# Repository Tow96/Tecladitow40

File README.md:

# Tecladitow-40

The Tecladitow40 is a simple 40% handwired ortholinear keyboard which utilizes 
[QMK](https://github.com/qmk/qmk_firmware) to communicate with any USB capable 
device. The Tecladitow40 is based on a Teensy2.0 microcontroller.

## Repository structure
The repository is divided in two subfolders, each containing a different part of 
the project. Further documentation can be found inside these folders.

1. [**Assembly**](/Assembly) - This folder contains the files that make up the 
physical keyboard. They are available in .SLDPRT and .STL formats.

2. [**Firmware**](/Firmware) - This folder contains the Hex file used to flash the
keyboard as well as a simple Test program to check the functionality of the keys.

## Future improvements
The specific improvements are separated by category inside the documentation for each folder.

- [ ] **Make rev1:** This revision will change the microcontroller to a pure 
ATmega32u4 and have a pcb.

## Credits
- Jose Tow [[@Tow96](https://github.com/Tow96)]

## License
This project is licensed under [GNU GPL-3.0](/LICENSE) as I believe in open source 
projects.

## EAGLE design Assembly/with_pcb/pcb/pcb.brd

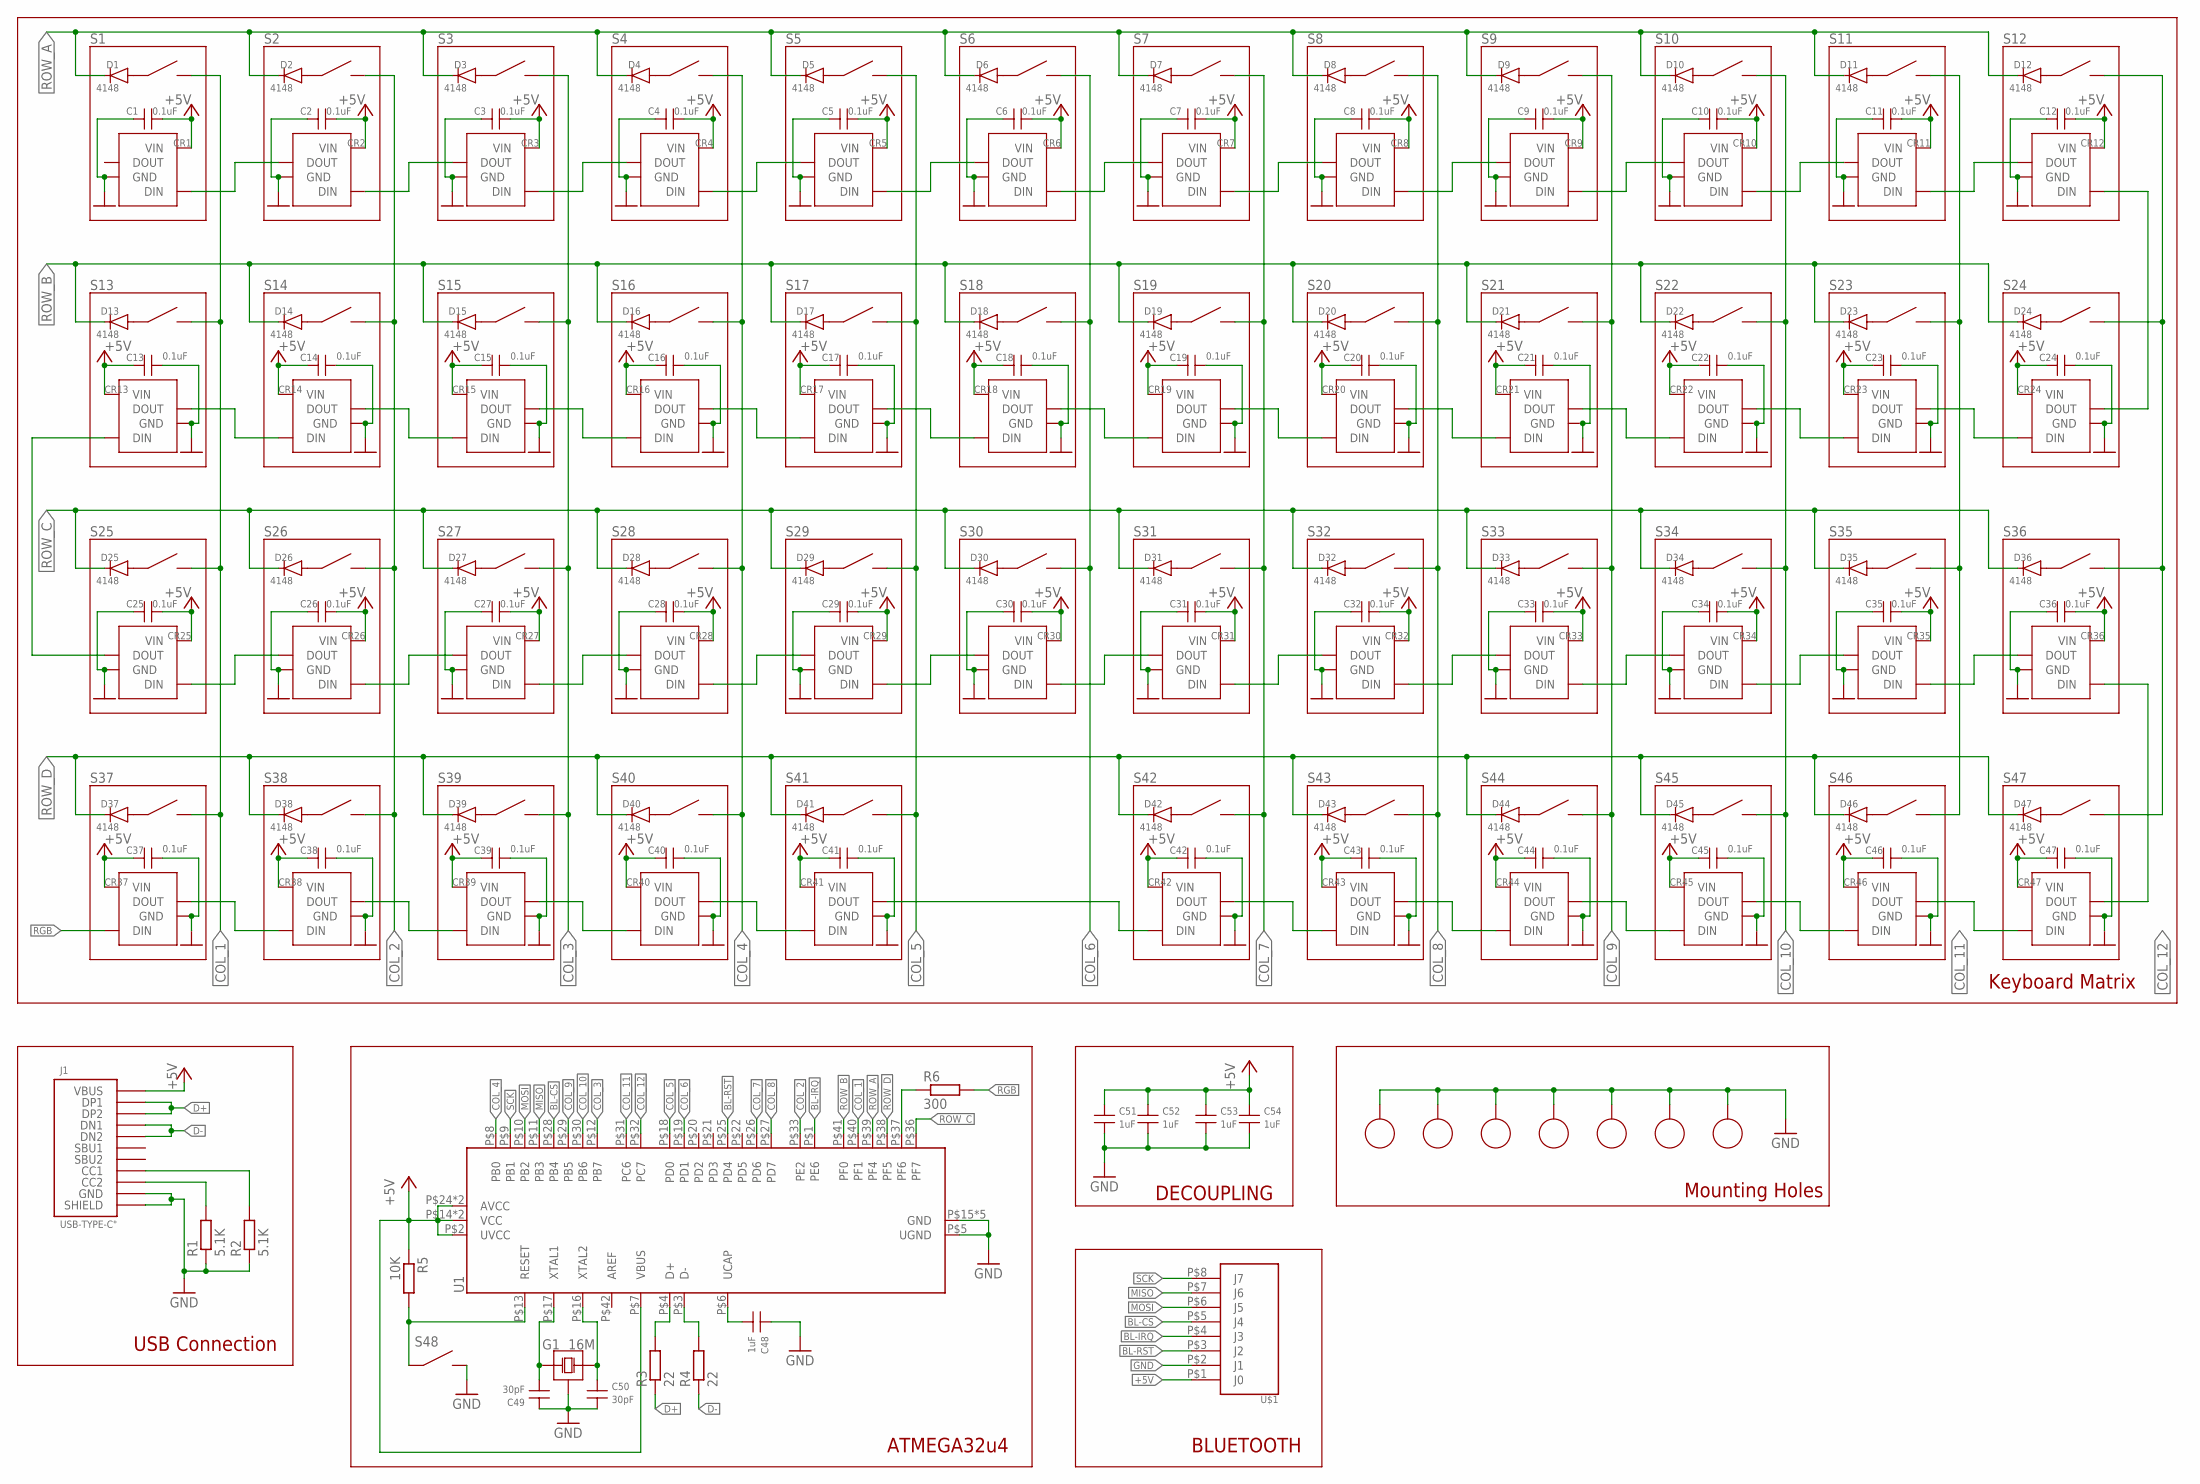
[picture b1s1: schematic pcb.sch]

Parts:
C1, C2, C3, C4, C5, C6, C7, C8, C9, C10, C11, C12, C13, C14, C15, C16, C17, C18, C19, C20, C21, C22, C23, C24, C25, C26, C27, C28, C29, C30, C31, C32, C33, C34, C35, C36, C37, C38, C39, C40, C41, C42, C43, C44, C45, C46, C47: 0.1uF; C0402
C48, C51, C52, C53, C54: 1uF; C0402
C49, C50: 30pF; C0402
CR1, CR2, CR3, CR4, CR5, CR6, CR7, CR8, CR9, CR10, CR11, CR12, CR13, CR14, CR15, CR16, CR17, CR18, CR19, CR20, CR21, CR22, CR23, CR24, CR25, CR26, CR27, CR28, CR29, CR30, CR31, CR32, CR33, CR34, CR35, CR36, CR37, CR38, CR39, CR40, CR41, CR42, CR43, CR44, CR45, CR46, CR47: SK6812MINI-E
D1, D2, D3, D4, D5, D6, D7, D8, D9, D10, D11, D12, D13, D14, D15, D16, D17, D18, D19, D20, D21, D22, D23, D24, D25, D26, D27, D28, D29, D30, D31, D32, D33, D34, D35, D36, D37, D38, D39, D40, D41, D42, D43, D44, D45, D46, D47: 4148; MINI_MELF
G1: 16M; SMD3225-4P
J1: USB-TYPE-C"; USB-C-SMD_TYPE-C16PIN
R1, R2: 5.1K; R0402
R3, R4: 22; R0402
R5: 10K; R0402
R6: 300; R0402
S1, S2, S3, S4, S5, S6, S7, S8, S9, S10, S11, S12, S13, S14, S15, S16, S17, S18, S19, S20, S21, S22, S23, S24, S25, S26, S27, S28, S29, S30, S31, S32, S33, S34, S35, S36, S37, S38, S39, S40, S41, S42, S43, S44, S45, S46, S47: MX_SWITCH
S48: SWITCH-SMD,3*4; SMD,3X4X2.0MM
U1: ATMEGA32U4-MUR; QFN-44_7X7X05P
U2, U3, U4, U5, U6, U7, U8: M2.5-HOLE; M2.5
U$1: JST-8PIN-SR; JST-SR-8PIN

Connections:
+5V: C1.P$2, C2.P$2, C3.P$2, C4.P$2, C5.P$2, C6.P$2, C7.P$2, C8.P$2, C9.P$2, C10.P$2, C11.P$2, C12.P$2, C13.P$1, C14.P$1, C15.P$1, C16.P$1, C17.P$1, C18.P$1, C19.P$1, C20.P$1, C21.P$1, C22.P$1, C23.P$1, C24.P$1, C25.P$2, C26.P$2, C27.P$2, C28.P$2, C29.P$2, C30.P$2, C31.P$2, C32.P$2, C33.P$2, C34.P$2, C35.P$2, C36.P$2, C37.P$1, C38.P$1, C39.P$1, C40.P$1, C41.P$1, C42.P$1, C43.P$1, C44.P$1, C45.P$1, C46.P$1, C47.P$1, C51.P$1, C52.P$1, C53.P$1, C54.P$1, CR1.P$1 (VIN), CR2.P$1 (VIN), CR3.P$1 (VIN), CR4.P$1 (VIN), CR5.P$1 (VIN), CR6.P$1 (VIN), CR7.P$1 (VIN), CR8.P$1 (VIN), CR9.P$1 (VIN), CR10.P$1 (VIN), CR11.P$1 (VIN), CR12.P$1 (VIN), CR13.P$1 (VIN), CR14.P$1 (VIN), CR15.P$1 (VIN), CR16.P$1 (VIN), CR17.P$1 (VIN), CR18.P$1 (VIN), CR19.P$1 (VIN), CR20.P$1 (VIN), CR21.P$1 (VIN), CR22.P$1 (VIN), CR23.P$1 (VIN), CR24.P$1 (VIN), CR25.P$1 (VIN), CR26.P$1 (VIN), CR27.P$1 (VIN), CR28.P$1 (VIN), CR29.P$1 (VIN), CR30.P$1 (VIN), CR31.P$1 (VIN), CR32.P$1 (VIN), CR33.P$1 (VIN), CR34.P$1 (VIN), CR35.P$1 (VIN), CR36.P$1 (VIN), CR37.P$1 (VIN), CR38.P$1 (VIN), CR39.P$1 (VIN), CR40.P$1 (VIN), CR41.P$1 (VIN), CR42.P$1 (VIN), CR43.P$1 (VIN), CR44.P$1 (VIN), CR45.P$1 (VIN), CR46.P$1 (VIN), CR47.P$1 (VIN), J1.A4B9 (VBUS), J1.B4A9 (VBUS), R5.P$1 (1), U1.P$2 (UVCC), U1.P$7 (VBUS), U1.P$14 (VCC), U1.P$24 (AVCC), U1.P$34 (VCC), U1.P$44 (AVCC), U$1.P$1 (J0)
BL-CS: U1.P$28 (PB4), U$1.P$5 (J4)
BL-IRQ: U1.P$1 (PE6), U$1.P$4 (J3)
BL-RST: U1.P$25 (PD4), U$1.P$3 (J2)
COL_1: S1.P$2, S13.P$2, S25.P$2, S37.P$2, U1.P$40 (PF1)
COL_2: S2.P$2, S14.P$2, S26.P$2, S38.P$2, U1.P$33 (PE2)
COL_3: S3.P$2, S15.P$2, S27.P$2, S39.P$2, U1.P$12 (PB7)
COL_4: S4.P$2, S16.P$2, S28.P$2, S40.P$2, U1.P$8 (PB0)
COL_5: S5.P$2, S17.P$2, S29.P$2, S41.P$2, U1.P$18 (PD0)
COL_6: S6.P$2, S18.P$2, S30.P$2, U1.P$19 (PD1)
COL_7: S7.P$2, S19.P$2, S31.P$2, S42.P$2, U1.P$26 (PD6)
COL_8: S8.P$2, S20.P$2, S32.P$2, S43.P$2, U1.P$27 (PD7)
COL_9: S9.P$2, S21.P$2, S33.P$2, S44.P$2, U1.P$29 (PB5)
COL_10: S10.P$2, S22.P$2, S34.P$2, S45.P$2, U1.P$30 (PB6)
COL_11: S11.P$2, S23.P$2, S35.P$2, S46.P$2, U1.P$31 (PC6)
COL_12: S12.P$2, S24.P$2, S36.P$2, S47.P$2, U1.P$32 (PC7)
D+: J1.A6 (DP1), J1.B6 (DP2), R3.P$1 (1)
D-: J1.A7 (DN1), J1.B7 (DN2), R4.P$1 (1)
GND: C1.P$1, C2.P$1, C3.P$1, C4.P$1, C5.P$1, C6.P$1, C7.P$1, C8.P$1, C9.P$1, C10.P$1, C11.P$1, C12.P$1, C13.P$2, C14.P$2, C15.P$2, C16.P$2, C17.P$2, C18.P$2, C19.P$2, C20.P$2, C21.P$2, C22.P$2, C23.P$2, C24.P$2, C25.P$1, C26.P$1, C27.P$1, C28.P$1, C29.P$1, C30.P$1, C31.P$1, C32.P$1, C33.P$1, C34.P$1, C35.P$1, C36.P$1, C37.P$2, C38.P$2, C39.P$2, C40.P$2, C41.P$2, C42.P$2, C43.P$2, C44.P$2, C45.P$2, C46.P$2, C47.P$2, C48.P$1, C49.P$1, C50.P$2, C51.P$2, C52.P$2, C53.P$2, C54.P$2, CR1.P$4 (GND), CR2.P$4 (GND), CR3.P$4 (GND), CR4.P$4 (GND), CR5.P$4 (GND), CR6.P$4 (GND), CR7.P$4 (GND), CR8.P$4 (GND), CR9.P$4 (GND), CR10.P$4 (GND), CR11.P$4 (GND), CR12.P$4 (GND), CR13.P$4 (GND), CR14.P$4 (GND), CR15.P$4 (GND), CR16.P$4 (GND), CR17.P$4 (GND), CR18.P$4 (GND), CR19.P$4 (GND), CR20.P$4 (GND), CR21.P$4 (GND), CR22.P$4 (GND), CR23.P$4 (GND), CR24.P$4 (GND), CR25.P$4 (GND), CR26.P$4 (GND), CR27.P$4 (GND), CR28.P$4 (GND), CR29.P$4 (GND), CR30.P$4 (GND), CR31.P$4 (GND), CR32.P$4 (GND), CR33.P$4 (GND), CR34.P$4 (GND), CR35.P$4 (GND), CR36.P$4 (GND), CR37.P$4 (GND), CR38.P$4 (GND), CR39.P$4 (GND), CR40.P$4 (GND), CR41.P$4 (GND), CR42.P$4 (GND), CR43.P$4 (GND), CR44.P$4 (GND), CR45.P$4 (GND), CR46.P$4 (GND), CR47.P$4 (GND), G1.P$2 (P2), G1.P$4 (P2), J1.A1B12 (GND), J1.B1A12 (GND), J1.SHIELD, J1.SHIELD1 (SHIELD), J1.SHIELD2 (SHIELD), J1.SHIELD3 (SHIELD), R1.P$1 (1), R2.P$1 (1), S48.P$2, U1.P$5 (UGND), U1.P$15 (GND), U1.P$23 (GND), U1.P$35 (GND), U1.P$43 (GND), U1.P$45 (GND), U2.P$1, U3.P$1, U4.P$1, U5.P$1, U6.P$1, U7.P$1, U8.P$1, U$1.P$2 (J1)
MISO: U1.P$11 (PB3), U$1.P$7 (J6)
MOSI: U1.P$10 (PB2), U$1.P$6 (J5)
unnamed: CR12.P$3 (DIN), CR24.P$2 (DOUT)
unnamed: CR13.P$3 (DIN), CR25.P$2 (DOUT)
unnamed: R3.P$2 (2), U1.P$4 (D+)
unnamed: J1.B5 (CC2), R1.P$2 (2)
unnamed: D1.P$2 (+), S1.P$1
unnamed: J1.A5 (CC1), R2.P$2 (2)
unnamed: R4.P$2 (2), U1.P$3 (D-)
unnamed: R5.P$2 (2), S48.P$1, U1.P$13 (RESET)
unnamed: CR1.P$3 (DIN), CR2.P$2 (DOUT)
unnamed: D2.P$2 (+), S2.P$1
unnamed: C48.P$2, U1.P$6 (UCAP)
unnamed: C49.P$2, G1.P$1 (P0), U1.P$17 (XTAL1)
unnamed: CR2.P$3 (DIN), CR3.P$2 (DOUT)
unnamed: D13.P$2 (+), S13.P$1
unnamed: R6.P$1 (1), U1.P$37 (PF6)
unnamed: CR13.P$2 (DOUT), CR14.P$3 (DIN)
unnamed: C50.P$1, G1.P$3 (P1), U1.P$16 (XTAL2)
unnamed: D20.P$2 (+), S20.P$1
unnamed: D3.P$2 (+), S3.P$1
unnamed: CR3.P$3 (DIN), CR4.P$2 (DOUT)
unnamed: CR19.P$2 (DOUT), CR20.P$3 (DIN)
unnamed: D14.P$2 (+), S14.P$1
unnamed: D4.P$2 (+), S4.P$1
unnamed: CR4.P$3 (DIN), CR5.P$2 (DOUT)
unnamed: CR14.P$2 (DOUT), CR15.P$3 (DIN)
unnamed: D5.P$2 (+), S5.P$1
unnamed: CR5.P$3 (DIN), CR6.P$2 (DOUT)
unnamed: D15.P$2 (+), S15.P$1
unnamed: CR15.P$2 (DOUT), CR16.P$3 (DIN)
unnamed: D6.P$2 (+), S6.P$1
unnamed: CR6.P$3 (DIN), CR7.P$2 (DOUT)
unnamed: D21.P$2 (+), S21.P$1
unnamed: CR20.P$2 (DOUT), CR21.P$3 (DIN)
unnamed: D7.P$2 (+), S7.P$1
unnamed: CR7.P$3 (DIN), CR8.P$2 (DOUT)
unnamed: D16.P$2 (+), S16.P$1
unnamed: CR27.P$3 (DIN), CR28.P$2 (DOUT)
unnamed: CR16.P$2 (DOUT), CR17.P$3 (DIN)
unnamed: D8.P$2 (+), S8.P$1
unnamed: CR8.P$3 (DIN), CR9.P$2 (DOUT)
unnamed: D17.P$2 (+), S17.P$1
unnamed: D9.P$2 (+), S9.P$1
unnamed: CR9.P$3 (DIN), CR10.P$2 (DOUT)
unnamed: CR17.P$2 (DOUT), CR18.P$3 (DIN)
unnamed: D22.P$2 (+), S22.P$1
unnamed: D10.P$2 (+), S10.P$1
unnamed: CR10.P$3 (DIN), CR11.P$2 (DOUT)
unnamed: CR21.P$2 (DOUT), CR22.P$3 (DIN)
unnamed: D18.P$2 (+), S18.P$1
unnamed: D11.P$2 (+), S11.P$1
unnamed: CR11.P$3 (DIN), CR12.P$2 (DOUT)
unnamed: D12.P$2 (+), S12.P$1
unnamed: D19.P$2 (+), S19.P$1
unnamed: CR18.P$2 (DOUT), CR19.P$3 (DIN)
unnamed: D23.P$2 (+), S23.P$1
unnamed: CR22.P$2 (DOUT), CR23.P$3 (DIN)
unnamed: D24.P$2 (+), S24.P$1
unnamed: CR23.P$2 (DOUT), CR24.P$3 (DIN)
unnamed: D25.P$2 (+), S25.P$1
unnamed: CR25.P$3 (DIN), CR26.P$2 (DOUT)
unnamed: D26.P$2 (+), S26.P$1
unnamed: CR26.P$3 (DIN), CR27.P$2 (DOUT)
unnamed: D27.P$2 (+), S27.P$1
unnamed: D28.P$2 (+), S28.P$1
unnamed: CR28.P$3 (DIN), CR29.P$2 (DOUT)
unnamed: D29.P$2 (+), S29.P$1
unnamed: CR29.P$3 (DIN), CR30.P$2 (DOUT)
unnamed: D30.P$2 (+), S30.P$1
unnamed: CR30.P$3 (DIN), CR31.P$2 (DOUT)
unnamed: D31.P$2 (+), S31.P$1
unnamed: CR31.P$3 (DIN), CR32.P$2 (DOUT)
unnamed: D32.P$2 (+), S32.P$1
unnamed: CR32.P$3 (DIN), CR33.P$2 (DOUT)
unnamed: D33.P$2 (+), S33.P$1
unnamed: CR33.P$3 (DIN), CR34.P$2 (DOUT)
unnamed: D34.P$2 (+), S34.P$1
unnamed: CR34.P$3 (DIN), CR35.P$2 (DOUT)
unnamed: D35.P$2 (+), S35.P$1
unnamed: CR35.P$3 (DIN), CR36.P$2 (DOUT)
unnamed: D36.P$2 (+), S36.P$1
unnamed: CR36.P$3 (DIN), CR47.P$2 (DOUT)
unnamed: D37.P$2 (+), S37.P$1
unnamed: D38.P$2 (+), S38.P$1
unnamed: CR37.P$2 (DOUT), CR38.P$3 (DIN)
unnamed: D39.P$2 (+), S39.P$1
unnamed: CR38.P$2 (DOUT), CR39.P$3 (DIN)
unnamed: D40.P$2 (+), S40.P$1
unnamed: CR39.P$2 (DOUT), CR40.P$3 (DIN)
unnamed: D41.P$2 (+), S41.P$1
unnamed: CR40.P$2 (DOUT), CR41.P$3 (DIN)
unnamed: D42.P$2 (+), S42.P$1
unnamed: CR41.P$2 (DOUT), CR42.P$3 (DIN)
unnamed: D43.P$2 (+), S43.P$1
unnamed: CR42.P$2 (DOUT), CR43.P$3 (DIN)
unnamed: D44.P$2 (+), S44.P$1
unnamed: CR43.P$2 (DOUT), CR44.P$3 (DIN)
unnamed: D45.P$2 (+), S45.P$1
unnamed: CR44.P$2 (DOUT), CR45.P$3 (DIN)
unnamed: D46.P$2 (+), S46.P$1
unnamed: CR45.P$2 (DOUT), CR46.P$3 (DIN)
unnamed: D47.P$2 (+), S47.P$1
unnamed: CR46.P$2 (DOUT), CR47.P$3 (DIN)
RGB: CR37.P$3 (DIN), R6.P$2 (2)
ROW_A: D1.P$1 (-), D2.P$1 (-), D3.P$1 (-), D4.P$1 (-), D5.P$1 (-), D6.P$1 (-), D7.P$1 (-), D8.P$1 (-), D9.P$1 (-), D10.P$1 (-), D11.P$1 (-), D12.P$1 (-), U1.P$39 (PF4)
ROW_B: D13.P$1 (-), D14.P$1 (-), D15.P$1 (-), D16.P$1 (-), D17.P$1 (-), D18.P$1 (-), D19.P$1 (-), D20.P$1 (-), D21.P$1 (-), D22.P$1 (-), D23.P$1 (-), D24.P$1 (-), U1.P$41 (PF0)
ROW_C: D25.P$1 (-), D26.P$1 (-), D27.P$1 (-), D28.P$1 (-), D29.P$1 (-), D30.P$1 (-), D31.P$1 (-), D32.P$1 (-), D33.P$1 (-), D34.P$1 (-), D35.P$1 (-), D36.P$1 (-), U1.P$36 (PF7)
ROW_D: D37.P$1 (-), D38.P$1 (-), D39.P$1 (-), D40.P$1 (-), D41.P$1 (-), D42.P$1 (-), D43.P$1 (-), D44.P$1 (-), D45.P$1 (-), D46.P$1 (-), D47.P$1 (-), U1.P$38 (PF5)
SCK: U1.P$9 (PB1), U$1.P$8 (J7)

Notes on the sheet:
Mounting Holes
Keyboard Matrix
USB Connection
ATMEGA32u4
DECOUPLING
BLUETOOTH

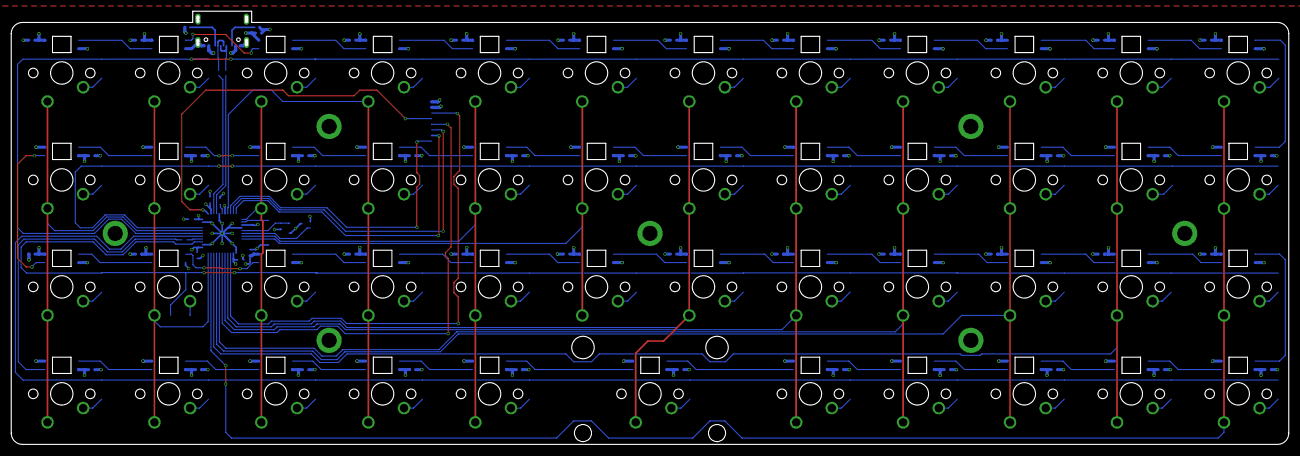
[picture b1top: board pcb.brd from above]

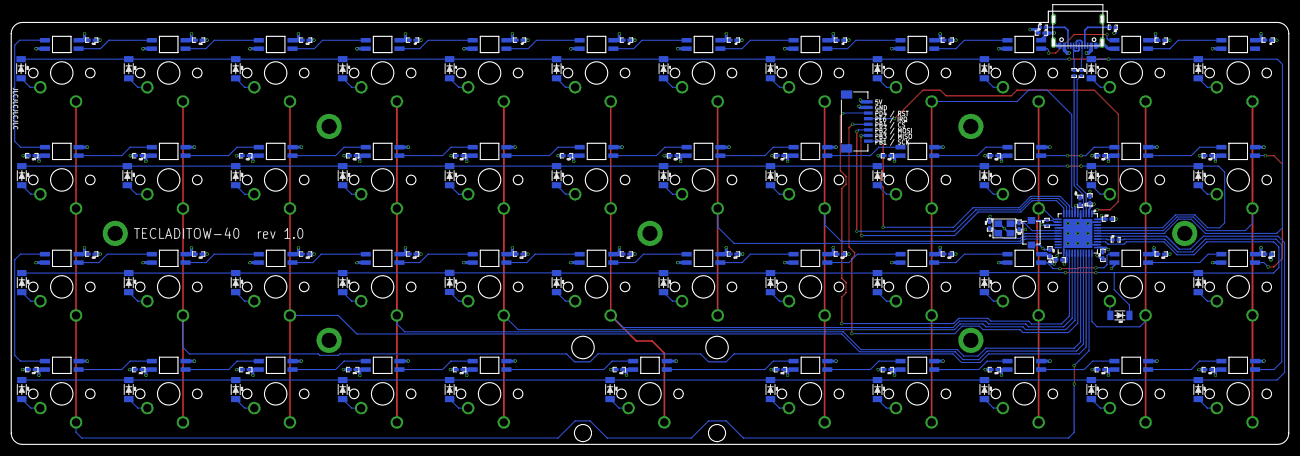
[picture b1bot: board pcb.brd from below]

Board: 4 copper layers, 227.5 x 77.2 mm, 213 parts (112 on the bottom side), 129 nets.

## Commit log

2021-04-28 Added rev0
2021-08-08 Moved hand soldered elements (rev0) to it's own folder
2021-08-08 Created eagle project for rev1
2021-08-08 Gave more space for connection between ground plane and USB connection
2021-08-09 Added informational BOM
    This BOM is not intended for sending to a PCB manufacturer
2021-08-09 Added the gerber files
2021-08-15 Made complete BOM
2021-08-15 Created assembly parts

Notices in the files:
README.md:
License: MIT
